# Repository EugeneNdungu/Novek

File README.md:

# Weather_Station_Novek

This is a schematic design of a low power Wi-Fi sensor node having temperature/humidity and pressure sensors along with a real time clock. It is powered by a li-on 4.2V battery.

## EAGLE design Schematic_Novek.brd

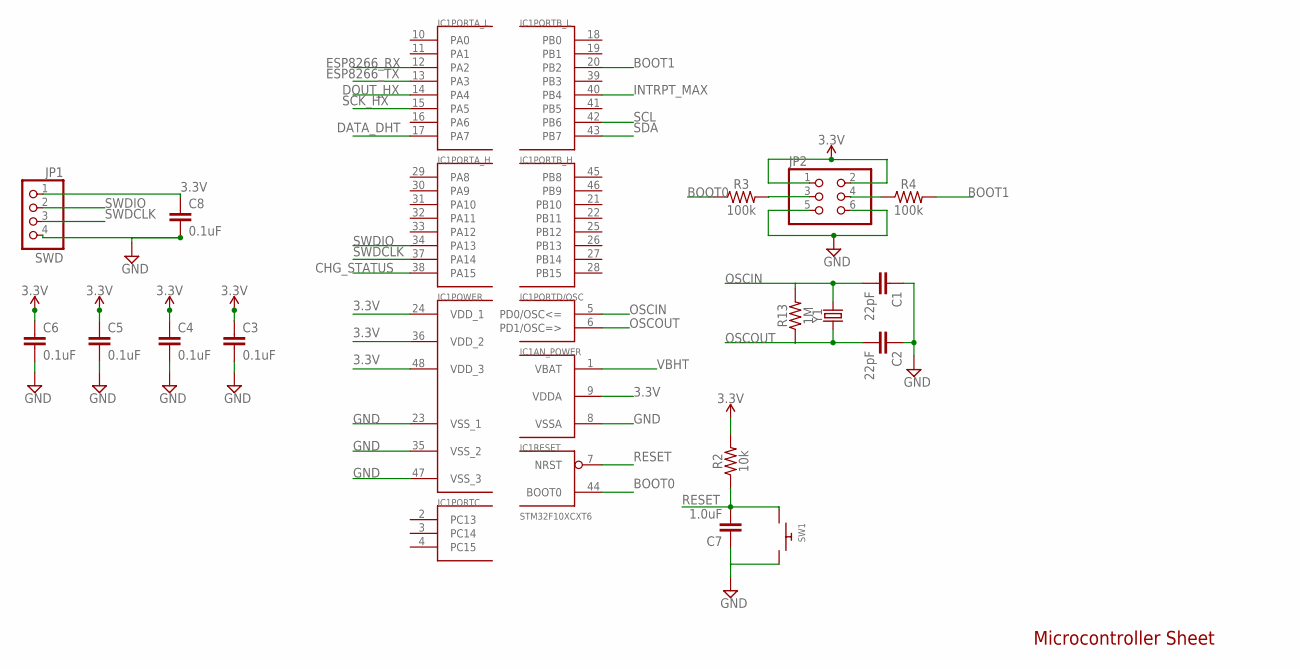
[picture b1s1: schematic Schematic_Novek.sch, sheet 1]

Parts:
C1, C2: 22pF; 0603
C3, C4, C5, C6, C8: 0.1uF; 0603
C7: 1.0uF; 0603
IC1: STM32F10XCXT6; TQFP48
JP1: SWD; 1X04/90
JP2: PINHD-2X3; 2X03
R2: 10k; 0603
R3, R4: 100k; 0603
R13: 1M; 0603
SW1: SWITCH_PUSHBUTTONC&K_KSS; BTN_CK_KSS
Y1: CRYSTALPTH-HC49UV; HC49U

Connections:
3.3V: C3.1, C4.1, C5.1, C6.1, C8.1, IC1.9 (VDDA), IC1.24 (VDD_1), IC1.36 (VDD_2), IC1.48 (VDD_3), JP1.1, JP2.1, JP2.2, R2.2; also elsewhere on the board
BOOT0: IC1.44 (BOOT0), R3.1
BOOT1: IC1.20 (PB2), R4.2
CHG_STATUS: IC1.38 (PA15); also elsewhere on the board
DATA_DHT: IC1.17 (PA7); also elsewhere on the board
DOUT_HX: IC1.14 (PA4); also elsewhere on the board
ESP8266_RX: IC1.12 (PA2); also elsewhere on the board
ESP8266_TX: IC1.13 (PA3); also elsewhere on the board
GND: C1.1, C2.1, C3.2, C4.2, C5.2, C6.2, C7.1, C8.2, IC1.8 (VSSA), IC1.23 (VSS_1), IC1.35 (VSS_2), IC1.47 (VSS_3), JP1.4, JP2.5, JP2.6, SW1.P$2; also elsewhere on the board
INTRPT_MAX: IC1.40 (PB4); also elsewhere on the board
unnamed: JP2.3, R3.2
unnamed: JP2.4, R4.1
OSCIN: C1.2, IC1.5 (PD0/OSC<=), R13.2, Y1.2
OSCOUT: C2.2, IC1.6 (PD1/OSC=>), R13.1, Y1.1
RESET: C7.2, IC1.7 (NRST), R2.1, SW1.P$1
SCK_HX: IC1.15 (PA5); also elsewhere on the board
SCL: IC1.42 (PB6); also elsewhere on the board
SDA: IC1.43 (PB7); also elsewhere on the board
SWDCLK: IC1.37 (PA14), JP1.3
SWDIO: IC1.34 (PA13), JP1.2
VBHT: IC1.1 (VBAT)

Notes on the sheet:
Microcontroller Sheet

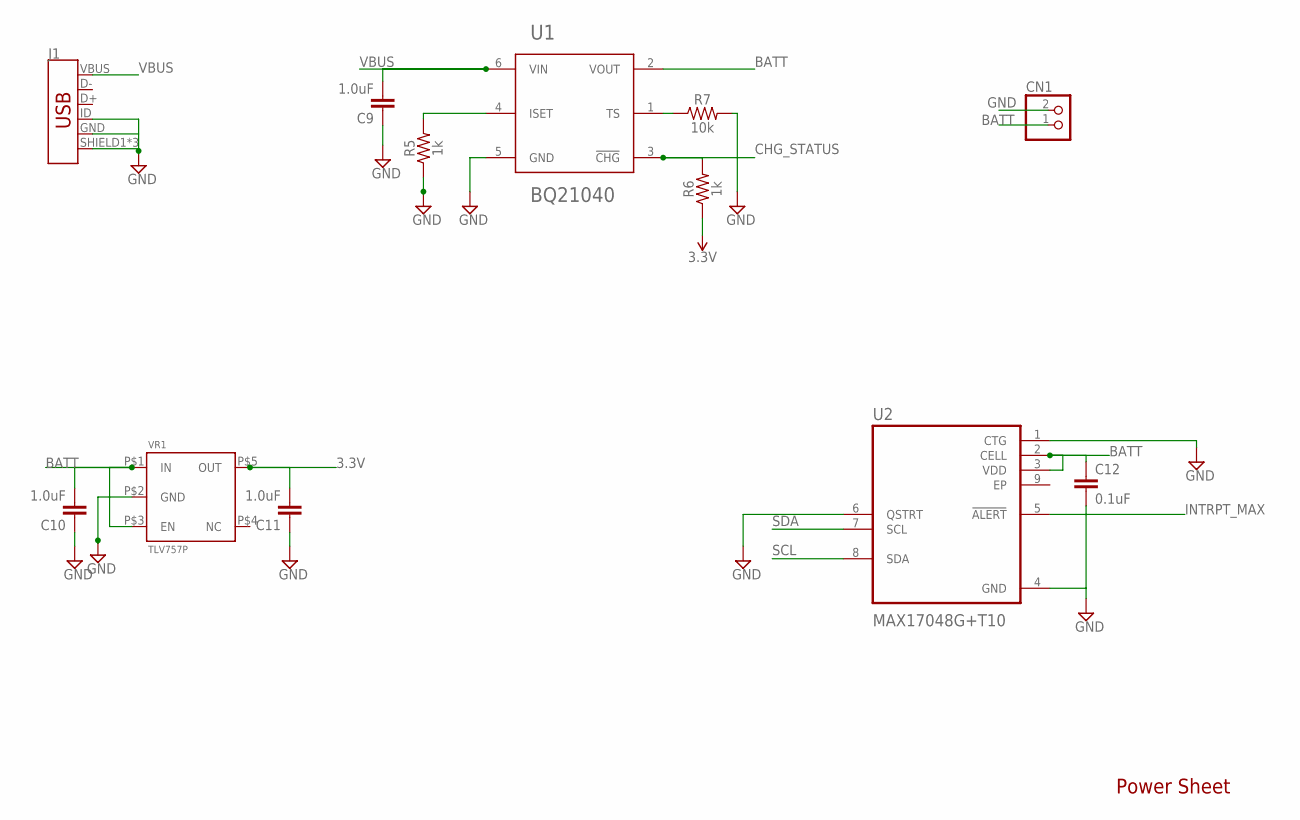
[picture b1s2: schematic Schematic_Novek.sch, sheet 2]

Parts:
C9, C10, C11: 1.0uF; 0603
C12: 0.1uF; 0603
CN1: JST_2PIN-THM; JST-PH-2-THM
J1: USB_MICRO-B_FEMALE-SMT; USB-B-MICRO-SMD
R5, R6: 1k; 0603
R7: 10k; 0603
U1: BQ21040; SOT23-6
U2: MAX17048G+T10; SON50P200X200X80-9N
VR1: TLV757P

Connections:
3.3V: C11.2, R6.1, VR1.P$5 (OUT); also elsewhere on the board
BATT: C10.2, C12.1, CN1.1 (2), U1.2 (VOUT), U2.2 (CELL), U2.3 (VDD), VR1.P$1 (IN), VR1.P$3 (EN)
CHG_STATUS: R6.2, U1.3 (!CHG!); also elsewhere on the board
EP: U2.9 (EP)
GND: C9.1, C10.1, C11.1, C12.2, CN1.2 (1), J1.GND, J1.ID, J1.SHIELD1 (SHIELD), J1.SHIELD2 (SHIELD), J1.SHIELD3 (SHIELD), R5.1, R7.2, U1.5 (GND), U2.1 (CTG), U2.4 (GND), U2.6 (QSTRT), VR1.P$2 (GND); also elsewhere on the board
INTRPT_MAX: U2.5 (!ALERT); also elsewhere on the board
unnamed: R5.2, U1.4 (ISET)
unnamed: R7.1, U1.1 (TS)
SCL: U2.8 (SDA); also elsewhere on the board
SDA: U2.7 (SCL); also elsewhere on the board
VBUS: C9.2, J1.VBUS, U1.6 (VIN)

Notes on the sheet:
Power Sheet

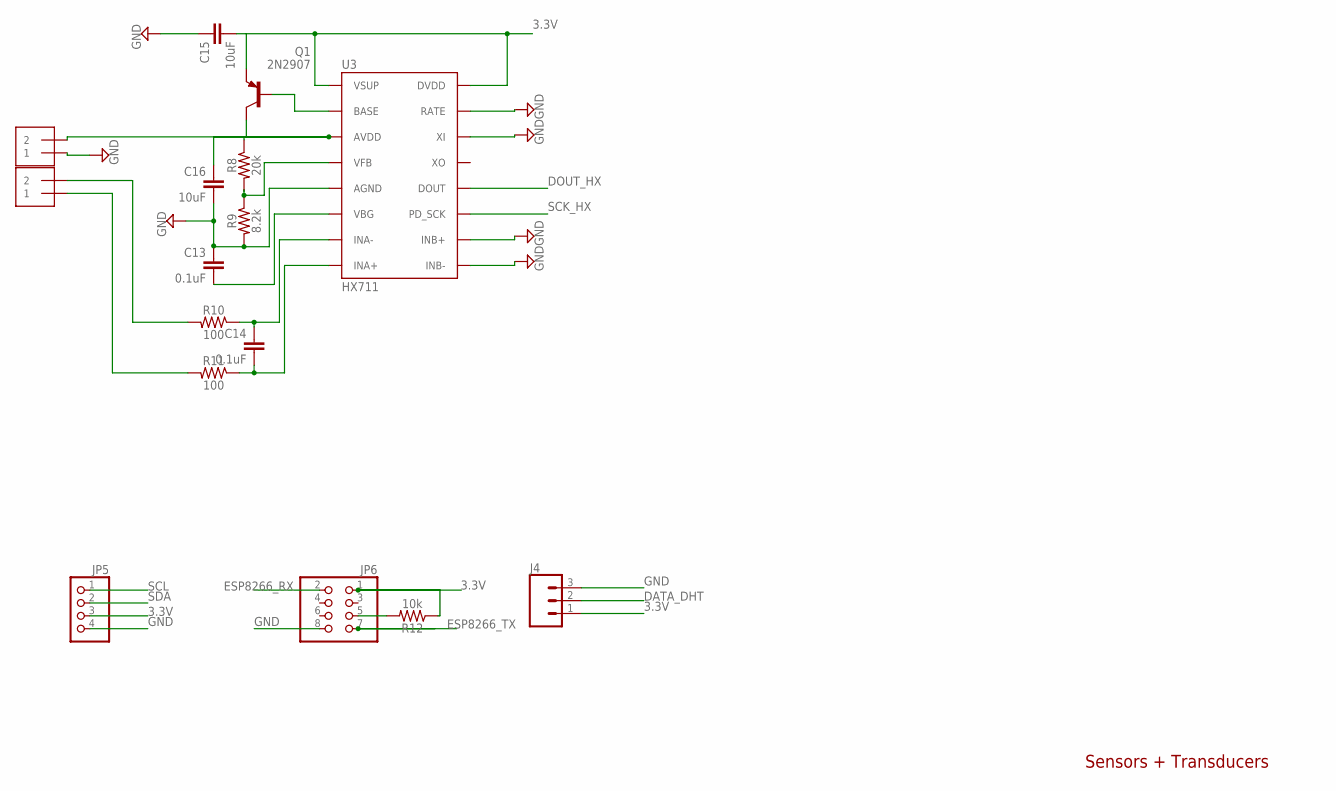
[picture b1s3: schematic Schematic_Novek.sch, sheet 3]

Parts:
C13, C14: 0.1uF; 0603
C15, C16: 10uF; 0603
J2, J3: 1X2-3.5MM
J4: CONN_03JST-PTH; JST-3-PTH
JP5: PINHD-1X4; 1X04
JP6: PINHD-2X4; 2X04
Q1: 2N2907; TO92-EBC-OVAL
R8: 20k; 0603
R9: 8.2k; 0603
R10, R11: 100; 0603
R12: 10k; 0603
U3: HX711; SO16

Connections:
3.3V: C15.2, J4.1, JP5.3, JP6.1, Q1.E, R12.1, U3.1 (VSUP), U3.16 (DVDD); also elsewhere on the board
DATA_DHT: J4.2; also elsewhere on the board
DOUT_HX: U3.12 (DOUT); also elsewhere on the board
ESP8266_RX: JP6.2; also elsewhere on the board
ESP8266_TX: JP6.7; also elsewhere on the board
GND: C13.1, C15.1, C16.2, J2.1, J4.3, JP5.4, JP6.8, R9.2, U3.5 (AGND), U3.9 (INB-), U3.10 (INB+), U3.14 (XI), U3.15 (RATE); also elsewhere on the board
unnamed: Q1.B, U3.2 (BASE)
unnamed: JP6.5, R12.2
unnamed: C16.1, J2.2, Q1.C, R8.1, U3.3 (AVDD)
unnamed: J3.2, R10.2
unnamed: J3.1, R11.2
unnamed: C13.2, U3.6 (VBG)
unnamed: R8.2, R9.1, U3.4 (VFB)
unnamed: C14.1, R10.1, U3.7 (INA-)
unnamed: C14.2, R11.1, U3.8 (INA+)
SCK_HX: U3.11 (PD_SCK); also elsewhere on the board
SCL: JP5.1; also elsewhere on the board
SDA: JP5.2; also elsewhere on the board

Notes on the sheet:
Sensors + Transducers

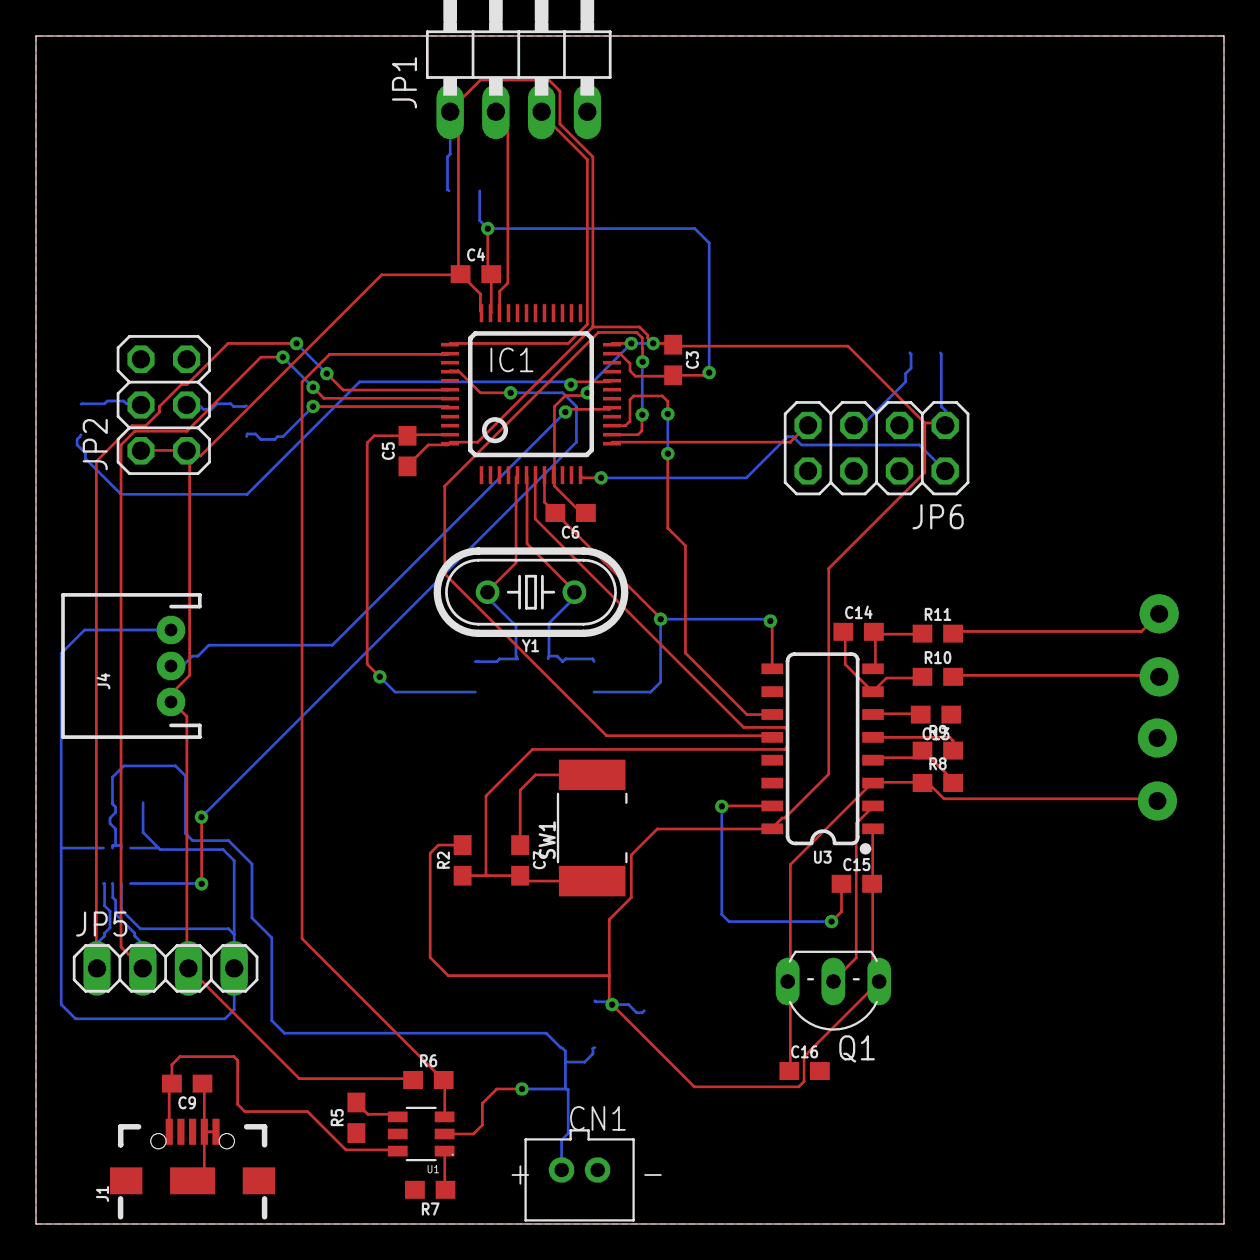
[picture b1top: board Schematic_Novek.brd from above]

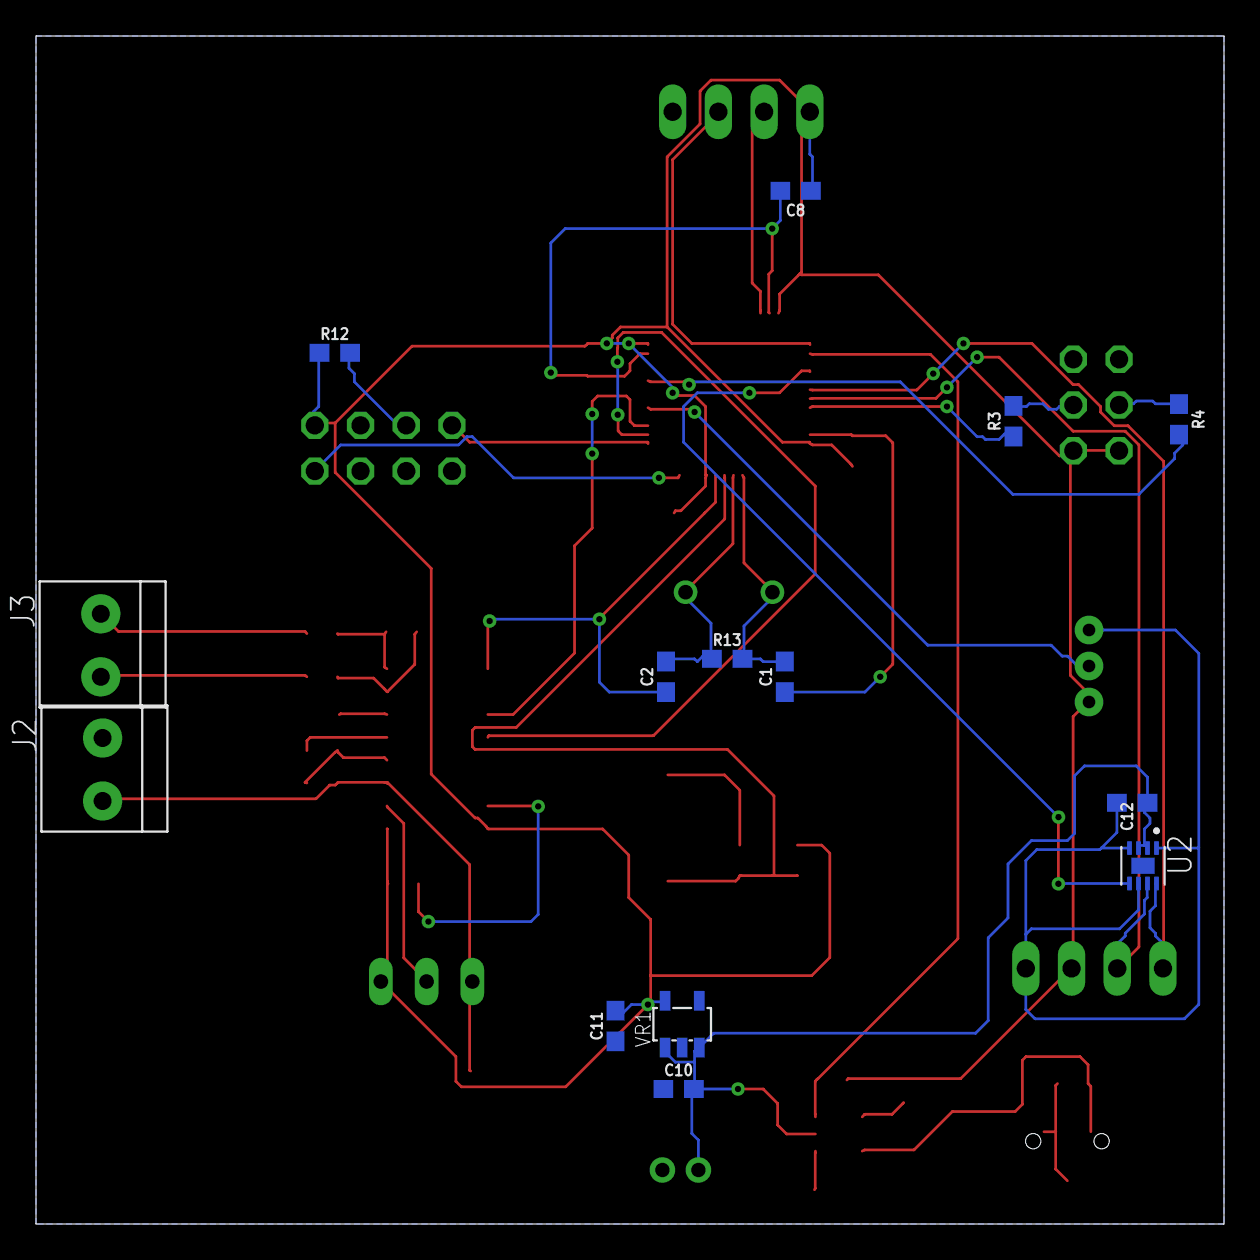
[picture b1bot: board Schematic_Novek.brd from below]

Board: 2 copper layers, 66.0 x 66.0 mm, 45 parts (14 on the bottom side), 33 nets.

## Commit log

2020-11-17 Adds schematic and brd files
2020-11-17 Adds frame
2020-11-17 Adds stm32f1 uC
2020-11-17 Adds HSE 8Mhz clock
2020-11-17 Adds power sheet
2020-11-17 Adds reset and power connections to uC
2020-11-17 Adds header pin for debugger
2020-11-26 Adds header pin to switch between the different bootable memories
2020-11-26 Adds bq21040
2020-11-26 adds 3.3V LDO
2020-11-26 Adds max17048 fuel gauge
2020-11-26 Adds new sensor sheet
2020-11-26 Adds pressure gauge
2020-11-26 Adds sensor ports
2020-11-26 Component placement on board
2020-11-26 Started routing
2020-11-26 Adds polygon for ground
2020-11-28 Routing of signals
2020-11-28 Completes routing
2020-12-26 Create README file
2020-12-27 Modifies README.md
2020-12-27 Deletes the .s#? and .b#? files
2020-12-28 Modifies routing

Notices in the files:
parts and their libraries:
SparkFun-Clocks: Licensing: Creative Commons ShareAlike 4.0 International - https://creativecommons.org/licenses/by-sa/4.0
